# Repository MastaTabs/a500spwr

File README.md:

# Amiga500 single power

This is a DCDC converter Module to fit in Rev. 6a+ Amiga 500 mainboards.
It will be soldered onto the mainboard and one can then use a 12V barrel jack power supply with the Amiga 500.

It can deliver upto 6A @ 5V and 500mA @ -12V. The 12V line is passed through.

It also adds a power switch to the machine on the backside.

It has been tested by me and was found to be working good.

### License
The Amiga500 single power documentation, including the design itself, is copyright © MastaTabs (Tobias Seiler) 2020.

Amiga500 single power is Open Hardware licensed under the CERN OHL v. 1.2.

You may redistribute and modify this documentation under the terms of the CERN OHL v.1.2. This documentation is distributed as is and WITHOUT ANY EXPRESS OR IMPLIED WARRANTIES whatsoever with respect to its functionality, operability or use, including, without limitation, any implied warranties OF MERCHANTABILITY, SATISFACTORY QUALITY, FITNESS FOR A PARTICULAR PURPOSE or infringement. We expressly disclaim any liability whatsoever for any direct, indirect, consequential, incidental or special damages, including, without limitation, lost revenues, lost profits, losses resulting from business interruption or loss of data, regardless of the form of action or legal theory under which the liability may be asserted, even if advised of the possibility or likelihood of such damages.

A copy of the full license is included in file LICENSE.pdf, please refer to it for applicable conditions. In order to properly deal with its terms, please see file LICENSE_HOWTO.pdf.

The contact points for information about manufactured Products (see section 4.2) are listed in file PRODUCT.md.

Any modifications made by Licensees (see section 3.4.b) shall be recorded in file CHANGES.md.

The Documentation Location of the original project is https://github.com/MastaTabs/a500spwr.

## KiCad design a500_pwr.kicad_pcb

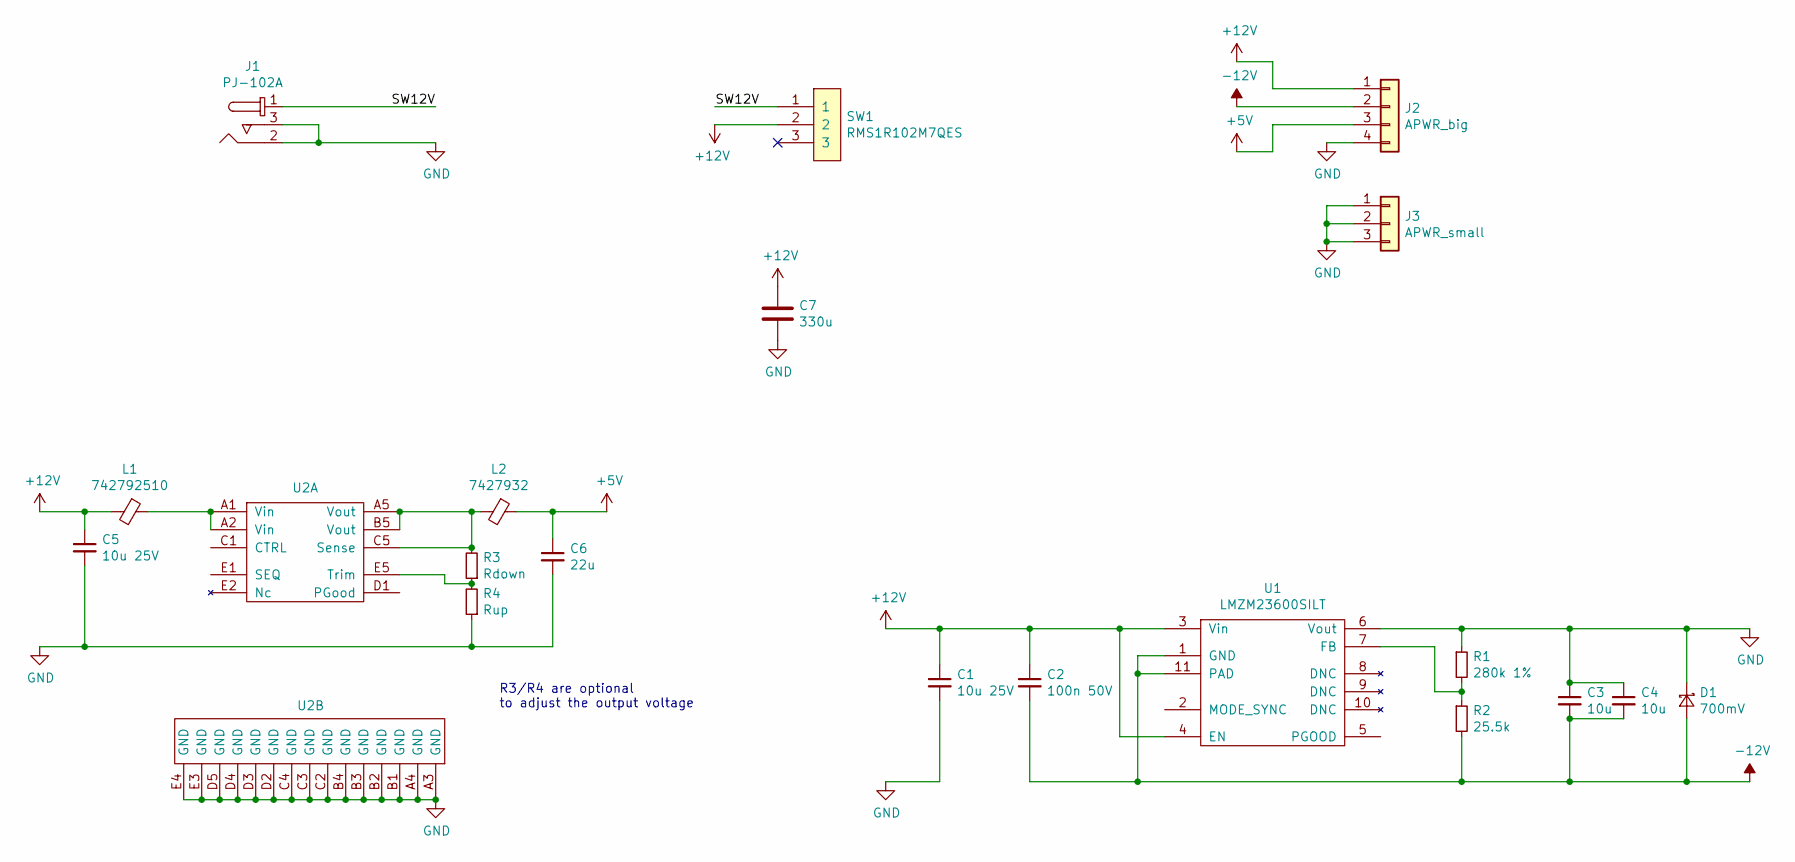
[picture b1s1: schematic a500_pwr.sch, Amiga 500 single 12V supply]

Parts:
C1, C5: 10u 25V; C_1206_HandSoldering
C2: 100n 50V; C_0805_HandSoldering
C3, C4: 10u; C_1206_HandSoldering
C6: 22u; C_1206_HandSoldering
C7: 330u; CP_Radial_D8.0mm_P3.50mm
D1: 700mV; D_SMA_Handsoldering
J1: PJ-102A; Barrel_Jack_5.5mmODx2.1mmID_PJ-102A; MPN PJ-102A; Digi-Key_PN CP-102A-ND
J2: APWR_big
J3: APWR_small
L1: 742792510; C_1812_HandSoldering; Digi-Key_PN 732-1640-1-ND
L2: 7427932; fb_5v; Digi-Key_PN 732-2394-1-ND
R1: 280k 1%; C_0603_HandSoldering
R2: 25.5k; C_0603_HandSoldering
R3: Rdown; C_0603_HandSoldering
R4: Rup; C_0603_HandSoldering
SW1: RMS1R102M7QES; rock_sw; Digi-Key_PN 450-2074-ND
U1: LMZM23600SILT; SIL0010A; Digi-Key_PN 296-49457-1-ND
U2: RPM5.0-6.0; Digi-Key_PN 945-3256-1-ND

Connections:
+5V: C6.1, J2.3, L2.1
+12V: C1.1, C2.1, C5.1, C7.1, J2.1, L1.2, SW1.2, U1.3 (Vin), U1.4 (EN)
-12V: C2.2, C3.2, C4.2, D1.2 (A), J2.2, R2.2, U1.1 (GND), U1.11 (PAD)
/SW12V: J1.1, SW1.1
GND: C1.2, C3.1, C4.1, C5.2, C6.2, C7.2, D1.1 (K), J1.2, J1.3, J2.4, J3.1, J3.2, J3.3, R1.1, R4.1, U1.6 (Vout), U2.A3 (GND), U2.A4 (GND), U2.B1 (GND), U2.B2 (GND), U2.B3 (GND), U2.B4 (GND), U2.C2 (GND), U2.C3 (GND), U2.C4 (GND), U2.D2 (GND), U2.D3 (GND), U2.D4 (GND), U2.D5 (GND), U2.E3 (GND), U2.E4 (GND)
unnamed: L1.1, U2.A1 (Vin), U2.A2 (Vin)
unnamed: L2.2, R3.2, U2.A5 (Vout), U2.B5 (Vout), U2.C5 (Sense)
unnamed: R1.2, R2.1, U1.7 (FB)
unnamed: R3.1, R4.2, U2.E5 (Trim)

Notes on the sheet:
R3/R4 are optional to adjust the output voltage

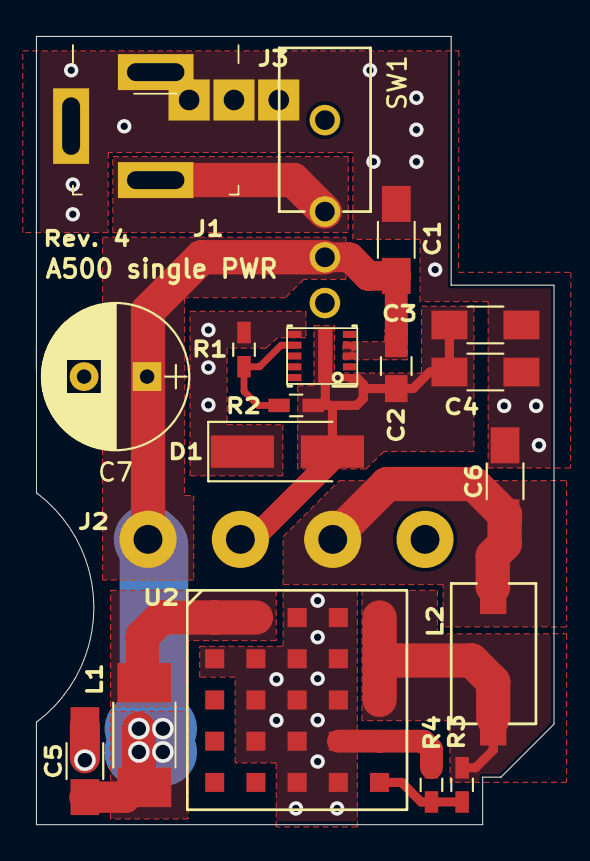
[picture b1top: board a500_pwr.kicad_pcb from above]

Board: 2 copper layers, 28.8 x 43.8 mm, 20 parts (0 on the bottom side), 9 nets.

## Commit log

2020-05-02 cleanup
2020-05-02 added inside picture to readme
2020-05-02 new BOM
2020-05-02 Waiver
2020-05-02 another cleanup
2020-05-02 add License
2020-05-03 add .gitignore
2020-05-16 adjust for different Barrel connector and note about R3/R4
2020-05-16 ignore bak's
2020-05-16 generated new gerbers (Rev. 3)
2020-09-08 the PGOOD pin of the LMZM23600 was numbered 11 but 5 buy mistake, now the planes are correctly drawn without manual connect of the center pad
2020-09-08 for real now with new gerbers
2020-09-15 slipped through with the last commit
2020-09-15 again slipped
2021-06-21 Fix C6 Mouser partnumber
2021-06-21 Fix C6 Mouser part number
2021-07-11 fix 22µF Mouser part number
2021-07-11 thickend all 12V and 5V traces
2021-07-11 rev4 gerbers
